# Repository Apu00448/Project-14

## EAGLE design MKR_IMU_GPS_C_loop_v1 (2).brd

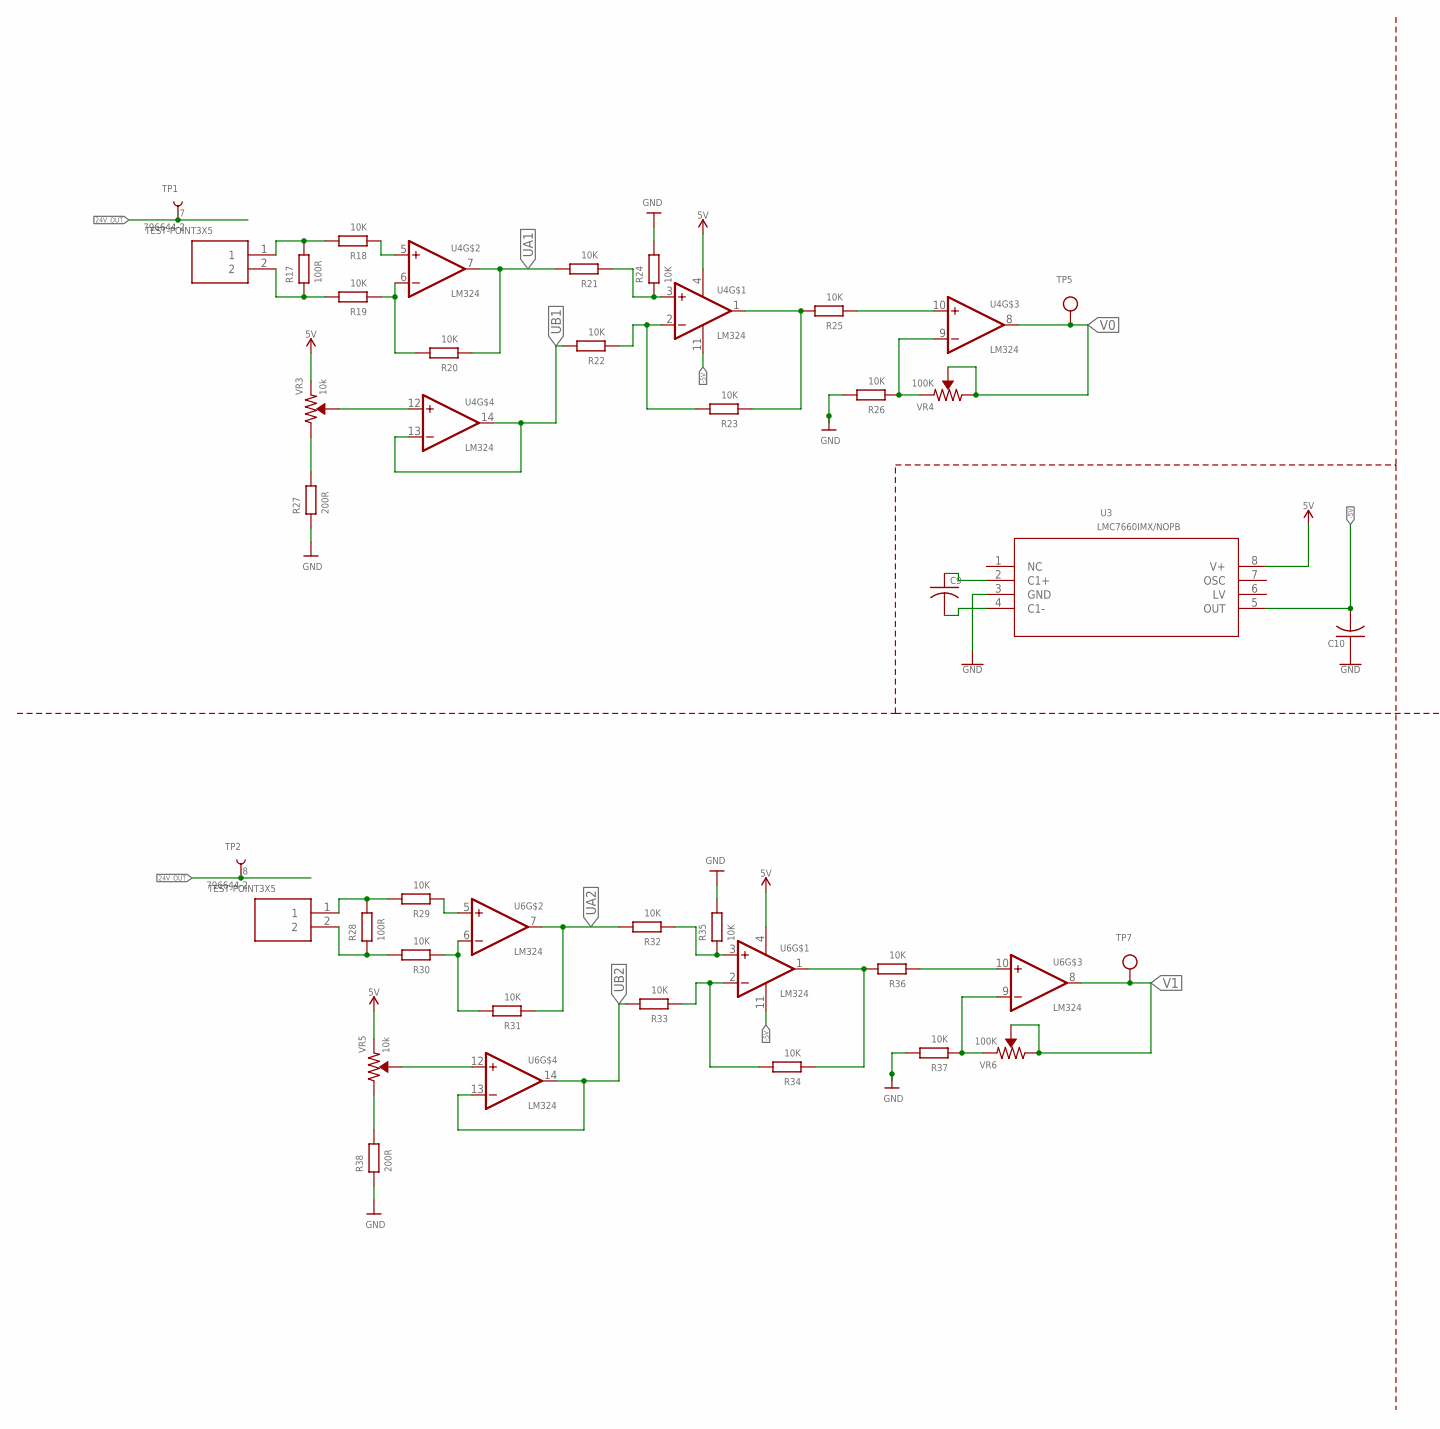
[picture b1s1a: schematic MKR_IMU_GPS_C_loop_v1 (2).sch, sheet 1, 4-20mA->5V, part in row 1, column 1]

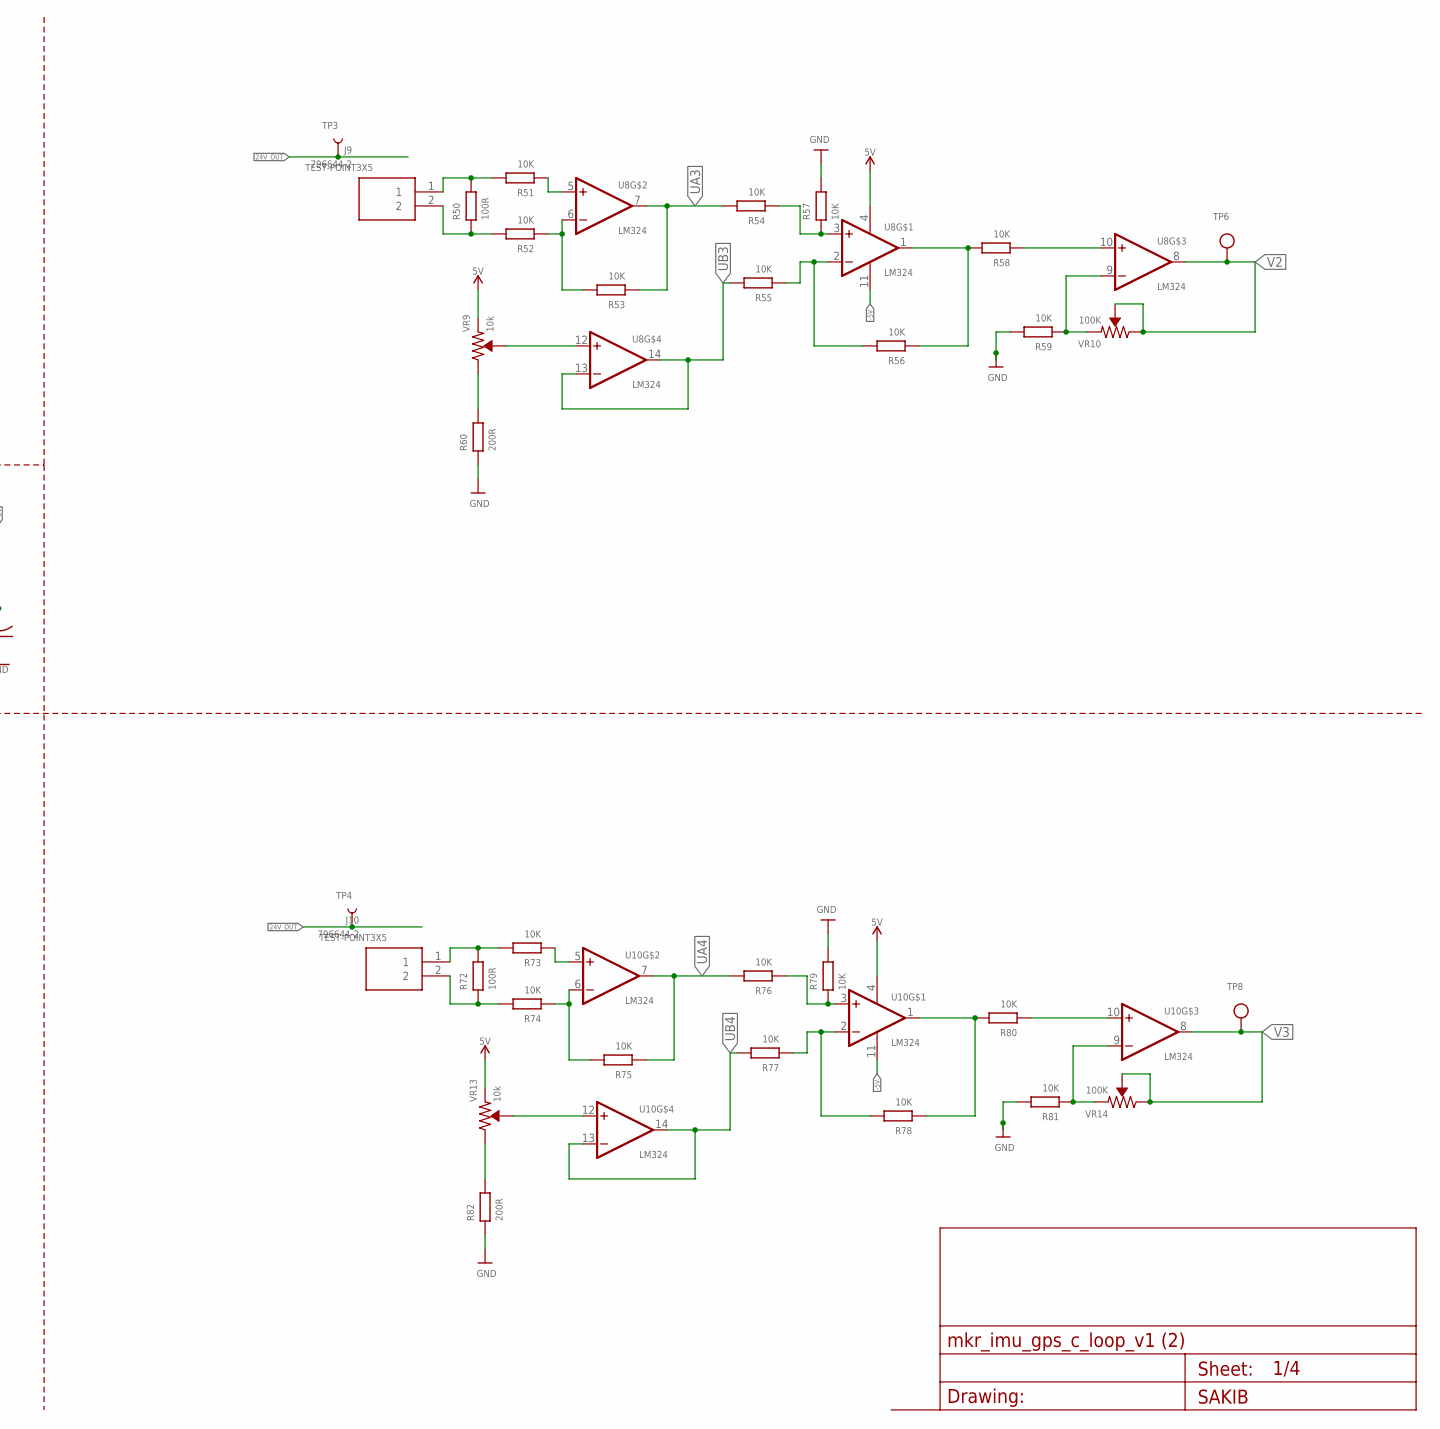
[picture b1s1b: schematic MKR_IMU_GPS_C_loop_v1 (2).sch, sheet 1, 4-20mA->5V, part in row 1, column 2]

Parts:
C9, C10: 10uF; C0402
J7, J8, J9, J10: 796644-2; 7966442
R17, R28, R50, R72: 100R; R0402
R18, R19, R20, R21, R22, R23, R24, R25, R26, R29, R30, R31, R32, R33, R34, R35, R36, R37, R51, R52, R53, R54, R55, R56, R57, R58, R59, R73, R74, R75, R76, R77, R78, R79, R80, R81: 10K; R0402
R27, R38, R60, R82: 200R; R0402
TP1, TP2, TP3, TP4: TEST-POINT3X5; PAD.03X.05
TP5, TP6, TP7, TP8: TESTPOINTROUND2MM; TESTPOINT_ROUND_2MM
U3: LMC7660IMX/NOPB; M08A_TEX
U4, U6, U8, U10: LM324; SOIC127P600X175-14N
VR3, VR5, VR9, VR13: 10k; TRIMPOT-SMD-3MM-CLOSED
VR4, VR6, VR10, VR14: 100K; TRIMPOT-SMD-3MM-CLOSED

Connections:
5V: U3.8 (V+), U4.4 (VCC+), U6.4 (VCC+), U8.4 (VCC+), U10.4 (VCC+), VR3.1 (CCW), VR5.1 (CCW), VR9.1 (CCW), VR13.1 (CCW); also elsewhere on the board
24V_OUT: TP1.1, TP2.1, TP3.1, TP4.1; also elsewhere on the board
-5V: C10.2, U3.5 (OUT), U4.11 (VCC-), U6.11 (VCC-), U8.11 (VCC-), U10.11 (VCC-)
GND: C10.1, R24.2, R26.2, R27.1, R35.2, R37.2, R38.1, R57.2, R59.2, R60.1, R79.2, R81.2, R82.1, U3.3 (GND); also elsewhere on the board
unnamed: C9.1, U3.2 (C1+)
unnamed: C9.2, U3.4 (C1-)
unnamed: J7.1, R17.2, R18.2
unnamed: J7.2, R17.1, R19.2
unnamed: R18.1, U4.5 (NON-INVERTING_INPUT2)
unnamed: R19.1, R20.2, U4.6 (INVERTING_INPUT2)
unnamed: R21.1, R24.1, U4.3 (NON-INVERTING_INPUT1)
unnamed: R23.1, R25.2, U4.1 (OUTPUT1)
unnamed: U4.12 (NON-INVERTING_INPUT4), VR3.2 (WIPER)
unnamed: R27.2, VR3.3 (CW)
unnamed: R22.1, R23.2, U4.2 (INVERTING_INPUT1)
unnamed: R25.1, U4.10 (NON-INVERTING_INPUT3)
unnamed: R26.1, U4.9 (INVERTING_INPUT3), VR4.1 (CCW)
unnamed: J8.1, R28.2, R29.2
unnamed: J8.2, R28.1, R30.2
unnamed: R29.1, U6.5 (NON-INVERTING_INPUT2)
unnamed: R30.1, R31.2, U6.6 (INVERTING_INPUT2)
unnamed: R32.1, R35.1, U6.3 (NON-INVERTING_INPUT1)
unnamed: R34.1, R36.2, U6.1 (OUTPUT1)
unnamed: U6.12 (NON-INVERTING_INPUT4), VR5.2 (WIPER)
unnamed: R38.2, VR5.3 (CW)
unnamed: R33.1, R34.2, U6.2 (INVERTING_INPUT1)
unnamed: R36.1, U6.10 (NON-INVERTING_INPUT3)
unnamed: R37.1, U6.9 (INVERTING_INPUT3), VR6.1 (CCW)
unnamed: J9.1, R50.2, R51.2
unnamed: J9.2, R50.1, R52.2
unnamed: R51.1, U8.5 (NON-INVERTING_INPUT2)
unnamed: R52.1, R53.2, U8.6 (INVERTING_INPUT2)
unnamed: R54.1, R57.1, U8.3 (NON-INVERTING_INPUT1)
unnamed: R56.1, R58.2, U8.1 (OUTPUT1)
unnamed: U8.12 (NON-INVERTING_INPUT4), VR9.2 (WIPER)
unnamed: R60.2, VR9.3 (CW)
unnamed: R55.1, R56.2, U8.2 (INVERTING_INPUT1)
unnamed: R58.1, U8.10 (NON-INVERTING_INPUT3)
unnamed: R59.1, U8.9 (INVERTING_INPUT3), VR10.1 (CCW)
unnamed: J10.1, R72.2, R73.2
unnamed: J10.2, R72.1, R74.2
unnamed: R73.1, U10.5 (NON-INVERTING_INPUT2)
unnamed: R74.1, R75.2, U10.6 (INVERTING_INPUT2)
unnamed: R76.1, R79.1, U10.3 (NON-INVERTING_INPUT1)
unnamed: R78.1, R80.2, U10.1 (OUTPUT1)
unnamed: U10.12 (NON-INVERTING_INPUT4), VR13.2 (WIPER)
unnamed: R82.2, VR13.3 (CW)
unnamed: R77.1, R78.2, U10.2 (INVERTING_INPUT1)
unnamed: R80.1, U10.10 (NON-INVERTING_INPUT3)
unnamed: R81.1, U10.9 (INVERTING_INPUT3), VR14.1 (CCW)
UA1: R20.1, R21.2, U4.7 (OUTPUT2)
UA2: R31.1, R32.2, U6.7 (OUTPUT2)
UA3: R53.1, R54.2, U8.7 (OUTPUT2)
UA4: R75.1, R76.2, U10.7 (OUTPUT2)
UB1: R22.2, U4.13 (INVERTING_INPUT4), U4.14 (OUTPUT4)
UB2: R33.2, U6.13 (INVERTING_INPUT4), U6.14 (OUTPUT4)
UB3: R55.2, U8.13 (INVERTING_INPUT4), U8.14 (OUTPUT4)
UB4: R77.2, U10.13 (INVERTING_INPUT4), U10.14 (OUTPUT4)
V0: TP5.P$1, U4.8 (OUTPUT3), VR4.2 (WIPER), VR4.3 (CW); also elsewhere on the board
V1: TP7.P$1, U6.8 (OUTPUT3), VR6.2 (WIPER), VR6.3 (CW); also elsewhere on the board
V2: TP6.P$1, U8.8 (OUTPUT3), VR10.2 (WIPER), VR10.3 (CW); also elsewhere on the board
V3: TP8.P$1, U10.8 (OUTPUT3), VR14.2 (WIPER), VR14.3 (CW); also elsewhere on the board

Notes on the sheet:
Sheet:
SAKIB
Drawing:

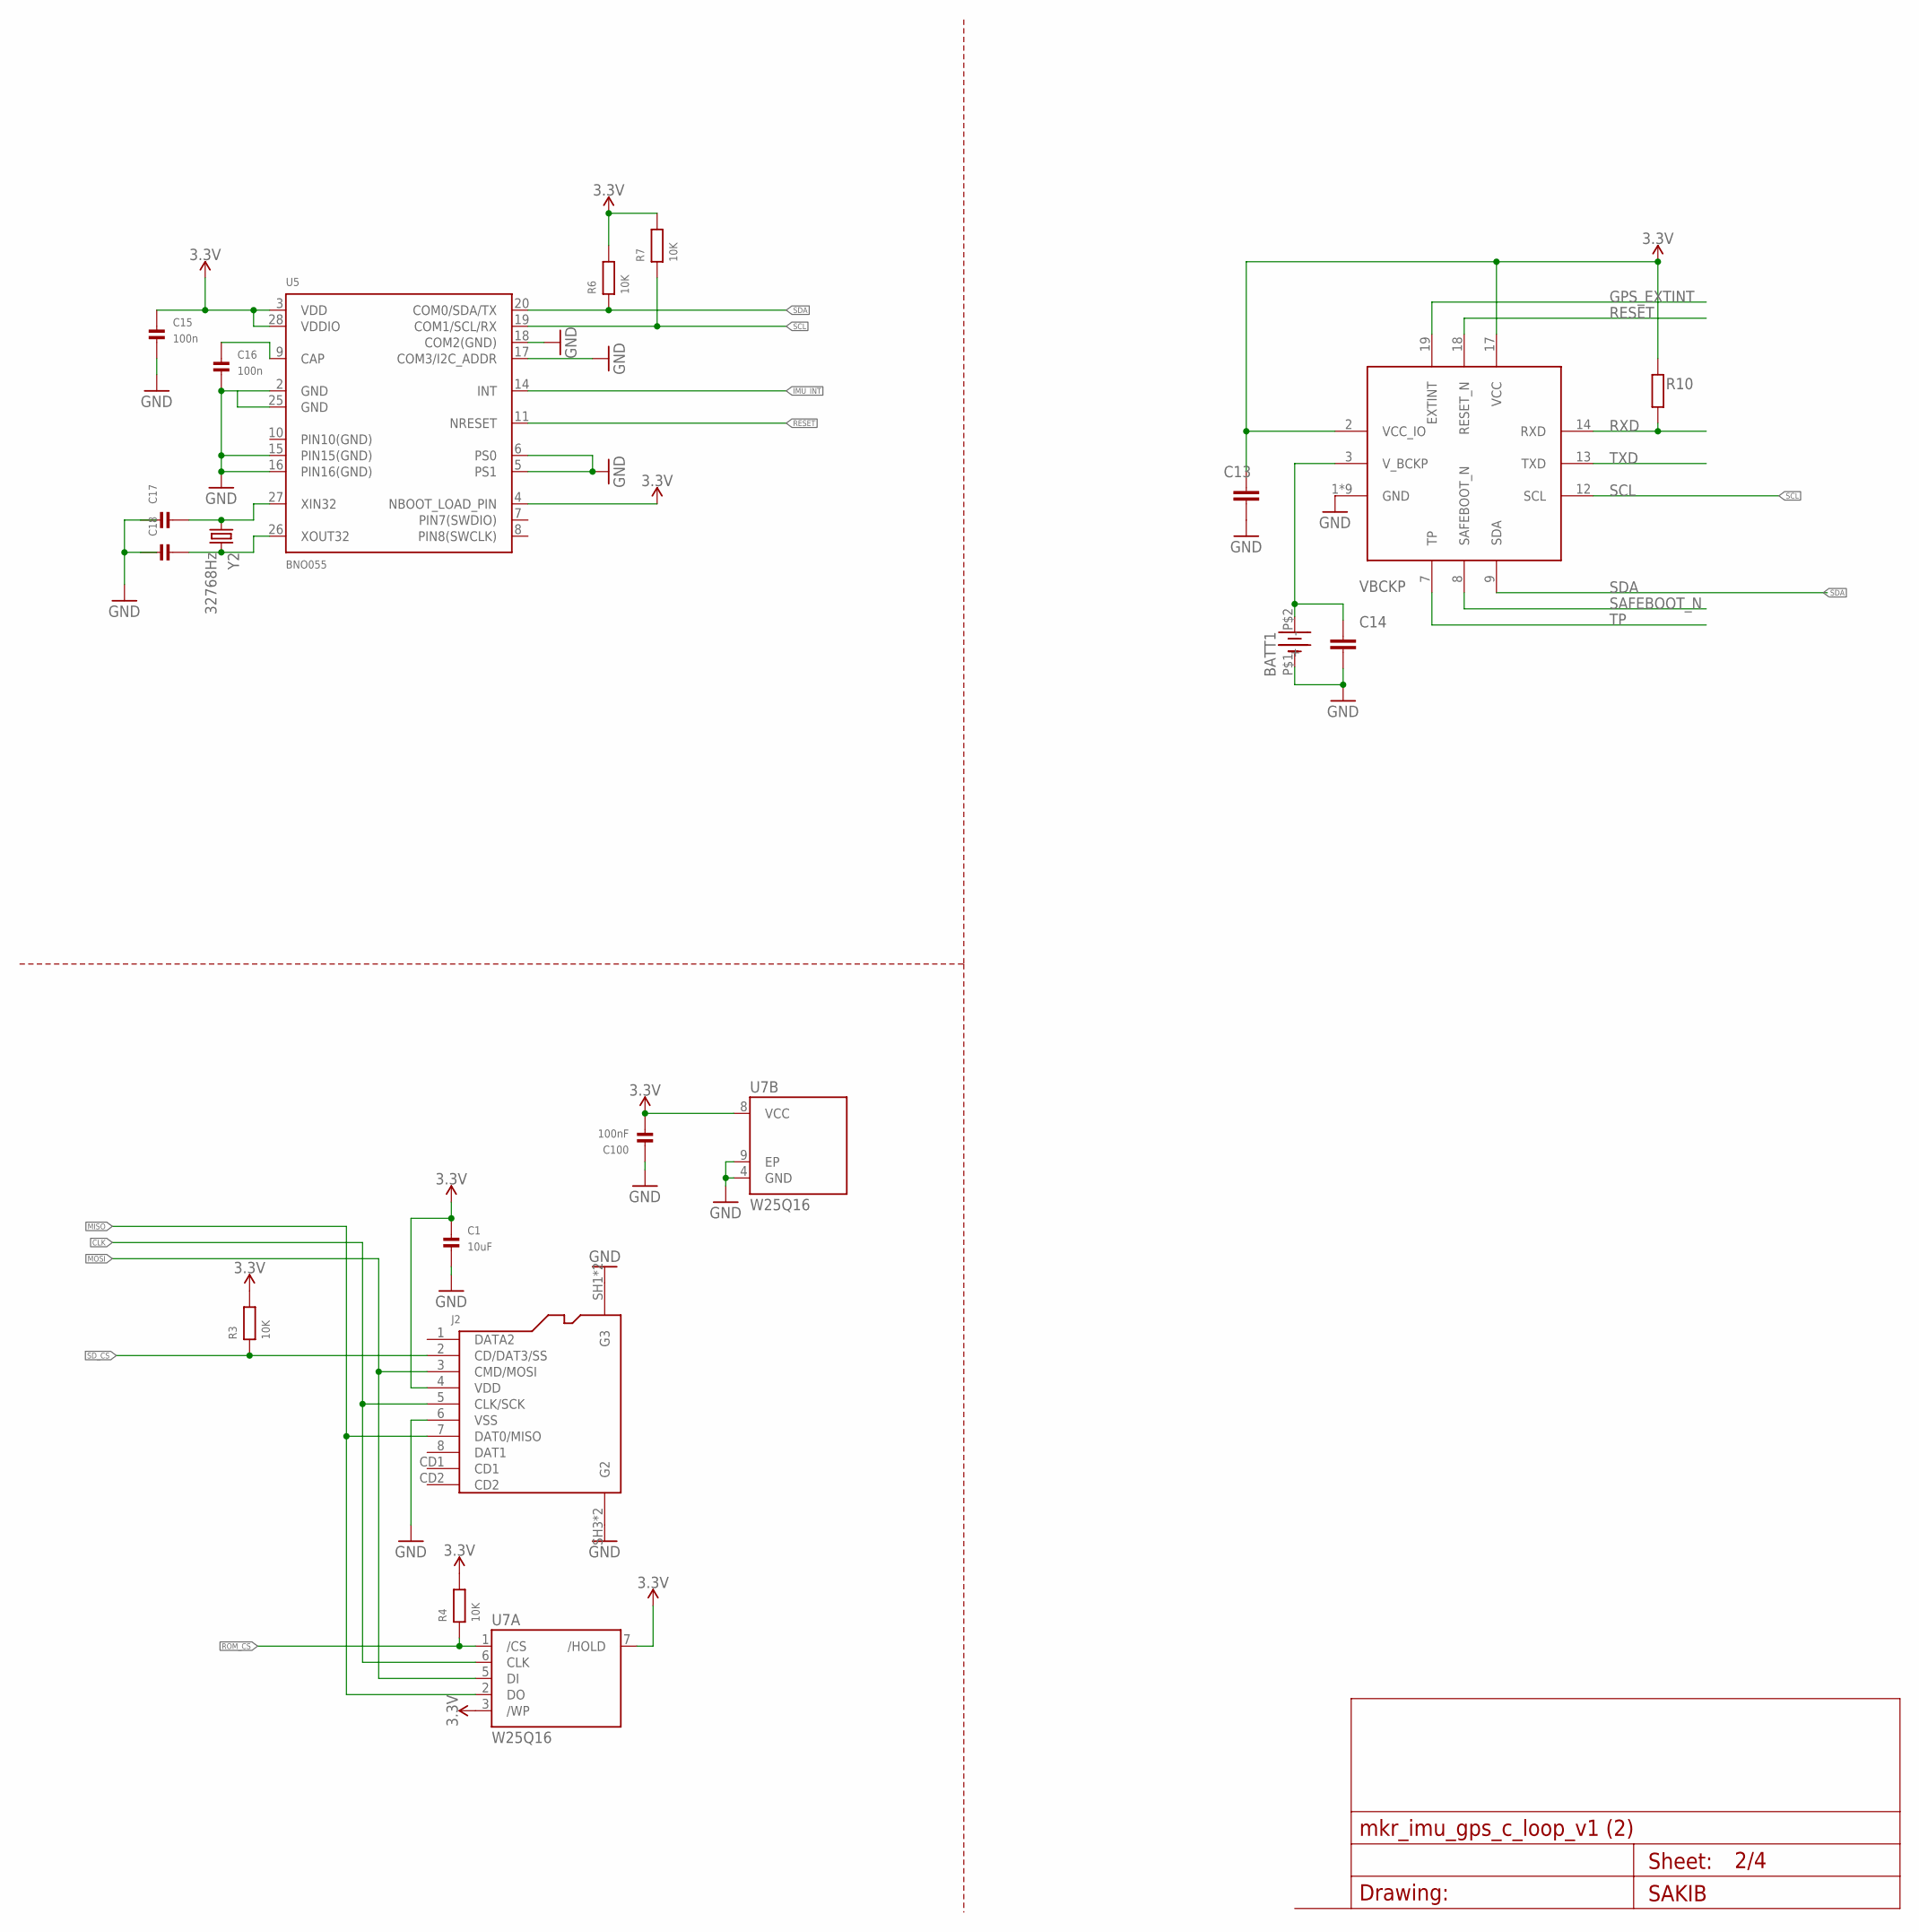
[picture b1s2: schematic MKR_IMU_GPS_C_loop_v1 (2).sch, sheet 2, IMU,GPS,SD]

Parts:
BATT1: BATT-HOLDER_12MM
C1: 10uF; _0603MP
C13: 100n; C0402
C14: 100n; C0402; VOLTAGE 25V
C15, C16: 100n; _0402MP
C17, C18: CAP_CERAMIC_0402MP; _0402MP
C100: 100nF; _0402MP
IC2: SAM-M8Q; UBLOXLIB_SAM-M8Q
J2: -; AMPHENOL_114-00841-68
R3, R4, R6, R7: 10K; R0402
R10: 100k; R0402; MPN RC0402FR-07100KL
U5: BNO055
U7: W25Q16; SON9P127_500X600X80L60X41T340X400N
Y2: 32768Hz; ABS07

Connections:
3.3V: C1.1, C13.1, C15.1, C100.2, IC2.2 (VCC_IO), IC2.17 (VCC), J2.4 (VDD), R3.2, R4.2, R6.2, R7.2, R10.2, U5.3 (VDD), U5.4 (NBOOT_LOAD_PIN), U5.28 (VDDIO), U7.3 (/WP), U7.7 (/HOLD), U7.8 (VCC); also elsewhere on the board
CLK: J2.5 (CLK/SCK), U7.6 (CLK); also elsewhere on the board
GND: BATT1.P$1 (-), C1.2, C13.2, C14.2, C15.2, C16.2, C17.1, C18.1, C100.1, IC2.1 (GND), IC2.4 (GND), IC2.5 (GND), IC2.6 (GND), IC2.10 (GND), IC2.11 (GND), IC2.15 (GND), IC2.16 (GND), IC2.20 (GND), J2.6 (VSS), J2.SH1 (G3), J2.SH2 (G3), J2.SH3 (G2), J2.SH4 (G2), U5.2 (GND), U5.5 (PS1), U5.6 (PS0), U5.15 (PIN15(GND)), U5.16 (PIN16(GND)), U5.17 (COM3/I2C_ADDR), U5.18 (COM2(GND)), U7.4 (GND), U7.9 (EP); also elsewhere on the board
GPS_EXTINT: IC2.19 (EXTINT); also elsewhere on the board
IMU_INT: U5.14 (INT); also elsewhere on the board
MISO: J2.7 (DAT0/MISO), U7.2 (DO); also elsewhere on the board
MOSI: J2.3 (CMD/MOSI), U7.5 (DI); also elsewhere on the board
unnamed: C17.2, U5.27 (XIN32), Y2.1
unnamed: C18.2, U5.26 (XOUT32), Y2.2
unnamed: C16.1, U5.9 (CAP)
RESET: IC2.18 (RESET_N), U5.11 (NRESET); also elsewhere on the board
ROM_CS: R4.1, U7.1 (/CS); also elsewhere on the board
RXD: IC2.14 (RXD), R10.1
SAFEBOOT_N: IC2.8 (SAFEBOOT_N)
SCL: IC2.12 (SCL), R7.1, U5.19 (COM1/SCL/RX); also elsewhere on the board
SDA: IC2.9 (SDA), R6.1, U5.20 (COM0/SDA/TX); also elsewhere on the board
SD_CS: J2.2 (CD/DAT3/SS), R3.1; also elsewhere on the board
TP: IC2.7 (TP)
TXD: IC2.13 (TXD)
VBCKP: BATT1.P$2 (+), C14.1, IC2.3 (V_BCKP)

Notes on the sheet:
Sheet:
SAKIB
Drawing:

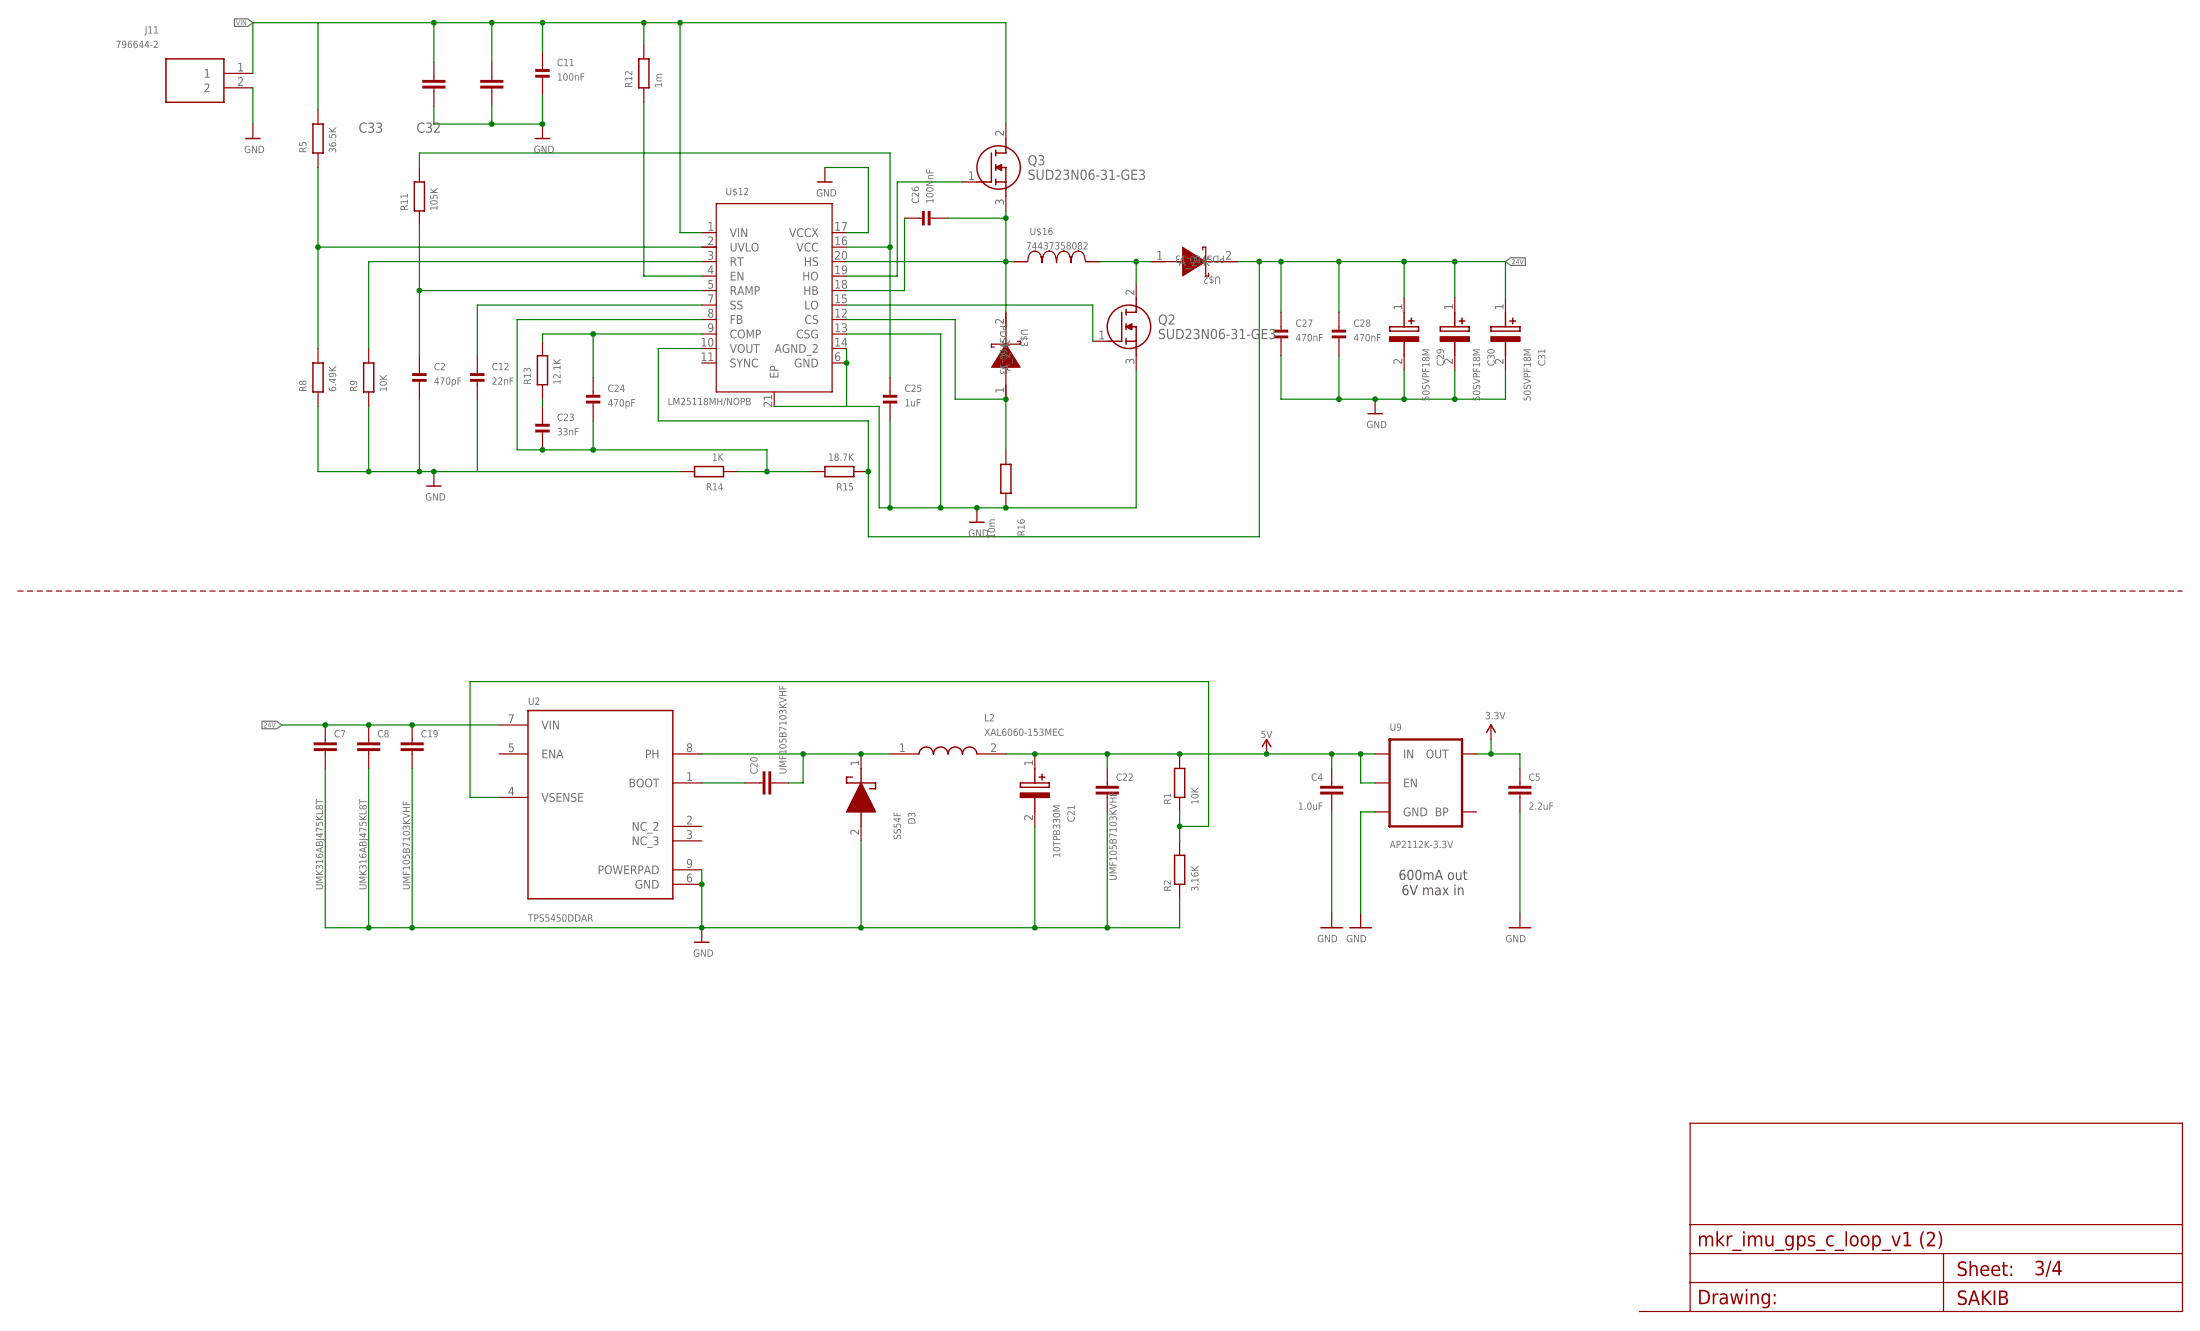
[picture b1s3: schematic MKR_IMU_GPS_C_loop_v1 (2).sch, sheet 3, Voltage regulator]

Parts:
C2, C24: 470pF; _0402MP
C4: 1.0uF; 0805
C5: 2.2uF; 0603
C7, C8: UMK316ABJ475KL8T; C1206
C11: 100nF; _0402MP
C12: 22nF; _0402MP
C19, C20, C22: UMF105B7103KVHF; C0402
C21: 10TPB330M; CAPPM7343X400N
C23: 33nF; _0402MP
C25: 1uF; _0402MP
C26: 100NnF; _0402MP
C27, C28: 470nF; _0402MP
C29, C30, C31: 50SVPF18M; 16SVF270M
C32, C33: C-EUC0402; C0402
D3: SS54F; SODFL4626X130N
J11: 796644-2; 7966442
L2: XAL6060-153MEC; XAL6060153MEC
Q2, Q3: SUD23N06-31-GE3; SUD23N0631GE3
R1, R9: 10K; R0402
R2: 3.16K; R0402
R5: 36.5K; R0402
R8: 6.49K; R0402
R11: 105K; R0402
R12: 1m; R0402
R13: 12.1K; R0402
R14: 1K; R0402
R15: 18.7K; R0402
R16: 10m; R0402
U2: TPS5450DDAR; CONV_TPS5450DDAR
U9: AP2112K-3.3V; SOT23-5
U$2, U$3: PDS760-13; POWERDI5
U$12: LM25118MH/NOPB; MXA20A
U$16: 74437358082; WE-LHMI_8040

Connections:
3.3V: C5.1, U9.5 (OUT); also elsewhere on the board
5V: C4.1, C21.1 (+), C22.1, L2.2, R1.2, U9.1 (IN), U9.3 (EN); also elsewhere on the board
24V: C7.1, C8.1, C19.1, C27.1, C28.1, C29.1 (+), C30.1 (+), C31.1 (+), R15.1, U2.7 (VIN), U$2.2 (K), U$12.10 (VOUT); also elsewhere on the board
GND: C2.2, C4.2, C5.2, C7.2, C8.2, C11.2, C12.2, C19.2, C21.2 (-), C22.2, C25.2, C27.2, C28.2, C29.2 (-), C30.2 (-), C31.2 (-), C32.1, C33.1, D3.2 (A), J11.2, Q2.3 (S), R2.1, R8.1, R9.1, R14.2, R16.2, U2.6 (GND), U2.9 (POWERPAD), U9.2 (GND), U$12.6 (GND), U$12.13 (CSG), U$12.14 (AGND_2), U$12.17 (VCCX), U$12.21 (EP); also elsewhere on the board
unnamed: C24.1, R13.2, U$12.9 (COMP)
unnamed: C23.1, R13.1
unnamed: C23.2, C24.2, R14.1, R15.2, U$12.8 (FB)
unnamed: C12.1, U$12.7 (SS)
unnamed: C20.1, U2.1 (BOOT)
unnamed: C20.2, D3.1 (K), L2.1, U2.8 (PH)
unnamed: C2.1, R11.1, U$12.5 (RAMP)
unnamed: R1.1, R2.2, U2.4 (VSENSE)
unnamed: C25.1, R11.2, U$12.16 (VCC)
unnamed: R9.2, U$12.3 (RT)
unnamed: R5.1, R8.2, U$12.2 (UVLO)
unnamed: R12.1, U$12.4 (EN)
unnamed: C26.1, U$12.18 (HB)
unnamed: Q3.1 (G), U$12.19 (HO)
unnamed: C26.2, Q3.3 (S), U$3.2 (K), U$12.20 (HS), U$16.2
unnamed: R16.1, U$3.1 (A_2), U$12.12 (CS)
unnamed: Q2.1 (G), U$12.15 (LO)
unnamed: Q2.2 (D), U$2.1 (A_2), U$16.1
VIN: C11.1, C32.2, C33.2, J11.1, Q3.2 (D), R5.2, R12.2, U$12.1 (VIN); also elsewhere on the board

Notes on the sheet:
600mA out 6V max in
Sheet:
SAKIB
Drawing:

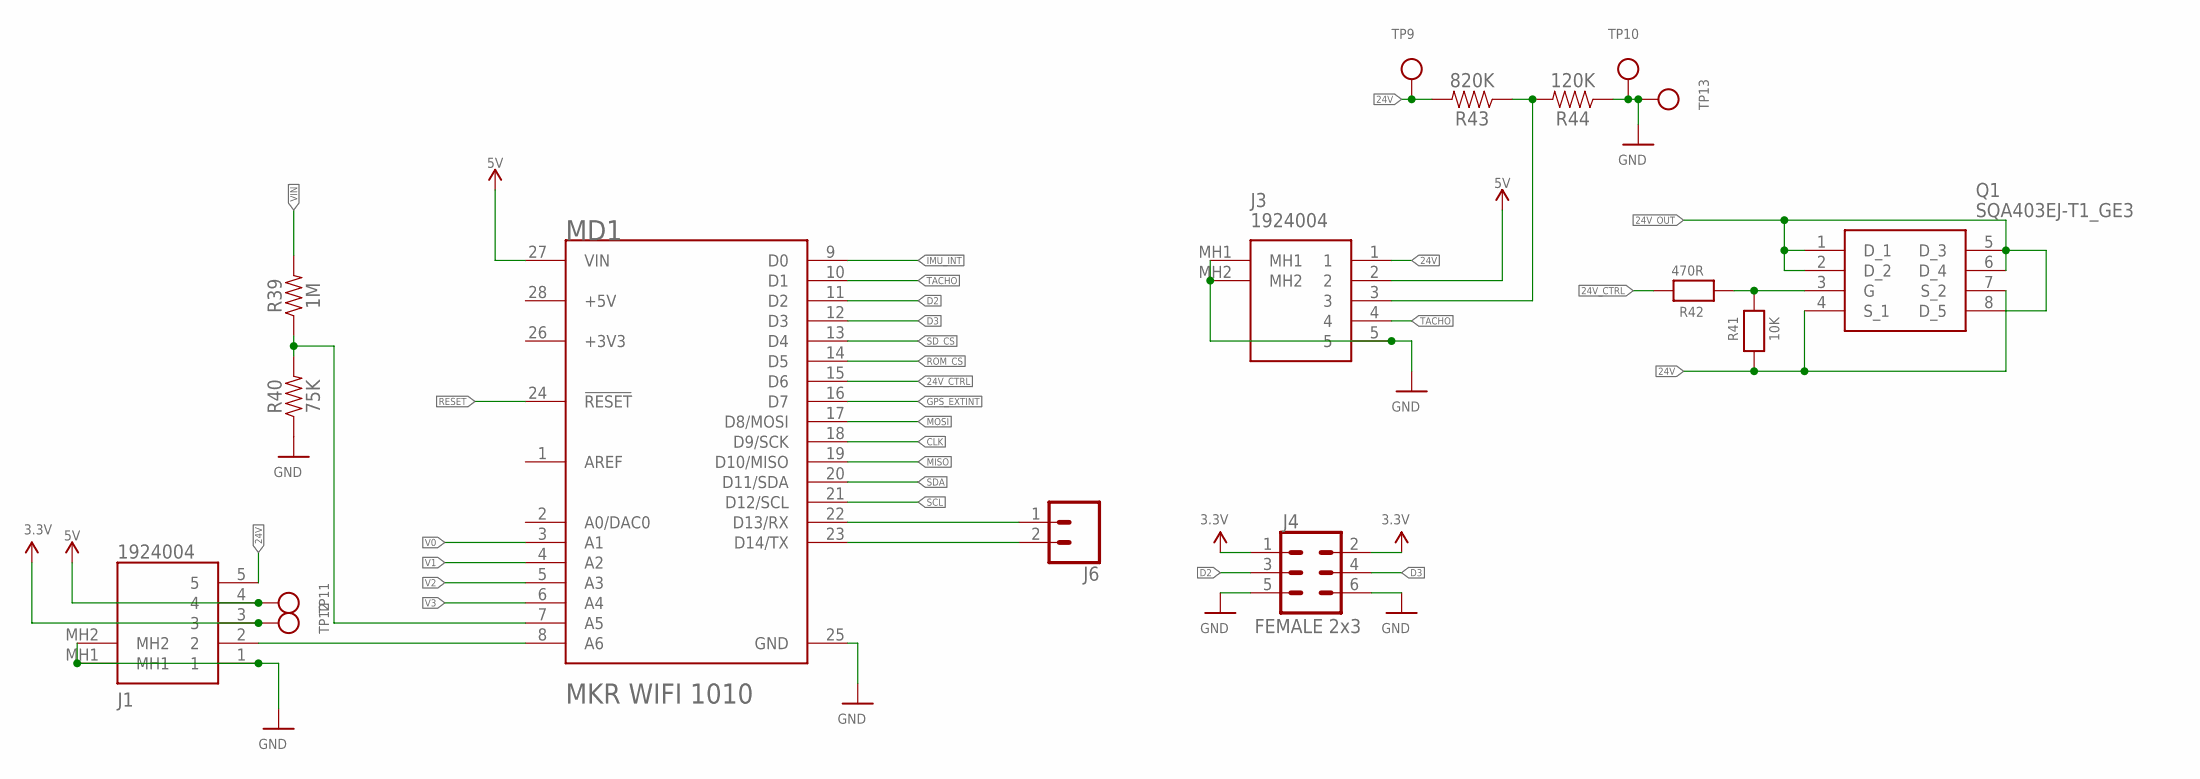
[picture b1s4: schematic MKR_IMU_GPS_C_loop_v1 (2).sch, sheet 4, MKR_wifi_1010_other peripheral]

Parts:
J1, J3: 1924004
J4: FEMALE 2x3; 2X3
J6: CONN_02; 1X02
MD1: ARDUINO_MKR_WIFI_1010ARDUINO_MKR_WIFI_1010_0_0; ARDUINO_MKR_WIFI_1010_0
Q1: SQA403EJ-T1_GE3; SQA403EJT1_GE3
R39: 1M; 0402-TIGHT
R40: 75K; 0402-TIGHT
R41: 10K; _0402MP
R42: 470R; _0402MP
R43: 820K; 0402-TIGHT
R44: 120K; 0402-TIGHT
TP9, TP10, TP11, TP12, TP13: TESTPOINTROUND2MM; TESTPOINT_ROUND_2MM

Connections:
3.3V: J1.3, J4.1, J4.2, TP12.P$1; also elsewhere on the board
5V: J1.4, J3.2, MD1.27 (VIN), TP11.P$1; also elsewhere on the board
24V: J1.5, J3.1, Q1.4 (S_1), Q1.7 (S_2), R41.1, R43.2, TP9.P$1; also elsewhere on the board
24V_CTRL: MD1.15 (D6), R42.2
24V_OUT: Q1.1 (D_1), Q1.2 (D_2), Q1.5 (D_3), Q1.6 (D_4), Q1.8 (D_5); also elsewhere on the board
+3V3: MD1.26 (+3V3)
+5V: MD1.28 (+5V)
CLK: MD1.18 (D9/SCK); also elsewhere on the board
D2: J4.3, MD1.11 (D2)
D3: J4.4, MD1.12 (D3)
GND: J1.1, J1.MH1, J1.MH2, J3.5, J3.MH1, J3.MH2, J4.5, J4.6, MD1.25 (GND), R40.1, R44.1, TP10.P$1, TP13.P$1; also elsewhere on the board
GPS_EXTINT: MD1.16 (D7); also elsewhere on the board
IMU_INT: MD1.9 (D0); also elsewhere on the board
MISO: MD1.19 (D10/MISO); also elsewhere on the board
MOSI: MD1.17 (D8/MOSI); also elsewhere on the board
unnamed: MD1.7 (A5), R39.1, R40.2
unnamed: J3.3, R43.1, R44.2
unnamed: J1.2, MD1.8 (A6)
unnamed: J6.1, MD1.22 (D13/RX)
unnamed: J6.2, MD1.23 (D14/TX)
RESET: MD1.24 (!RESET!); also elsewhere on the board
ROM_CS: MD1.14 (D5); also elsewhere on the board
SCL: MD1.21 (D12/SCL); also elsewhere on the board
SDA: MD1.20 (D11/SDA); also elsewhere on the board
SD_CS: MD1.13 (D4); also elsewhere on the board
TACHO: J3.4, MD1.10 (D1)
V0: MD1.3 (A1); also elsewhere on the board
V1: MD1.4 (A2); also elsewhere on the board
V2: MD1.5 (A3); also elsewhere on the board
V3: MD1.6 (A4); also elsewhere on the board
VIN: R39.2; also elsewhere on the board
X: Q1.3 (G), R41.2, R42.1

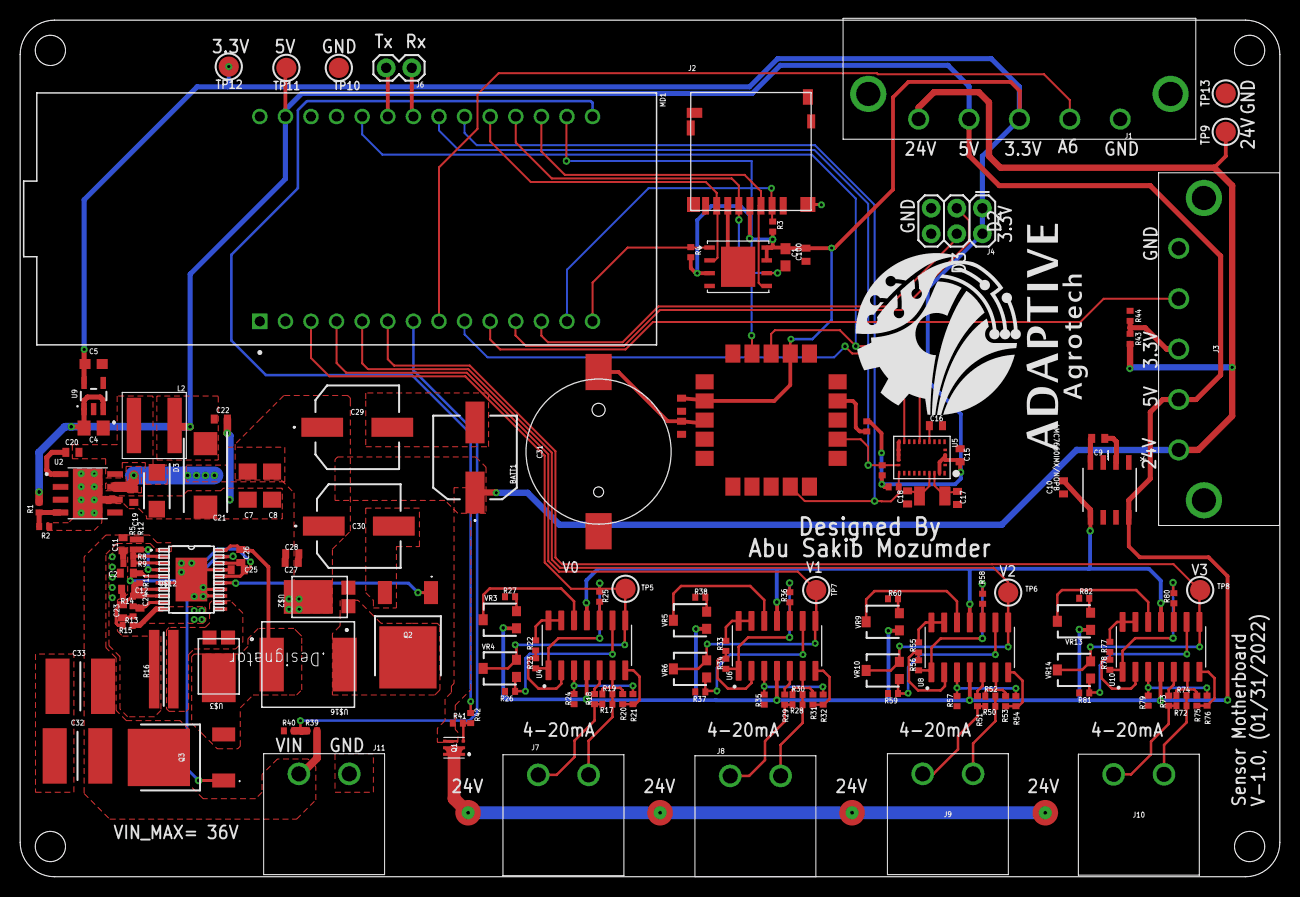
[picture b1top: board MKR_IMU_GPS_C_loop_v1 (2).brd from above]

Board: 2 copper layers, 125.0 x 85.0 mm, 151 parts (0 on the bottom side), 108 nets.

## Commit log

2024-01-03 MKR-IMU-Board -Eagle

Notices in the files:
parts and their libraries:
Arduino-Sensors: Copyright (c) 2016-2017 Arduino LLC.  All right reserved.
microbuilder: This work is placed in the public domain, and may be freely used for commercial and non-commercial work with the following conditions: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
COPYRIGHT: Copyright (C) 2022 Ultra Librarian. All rights reserved.
